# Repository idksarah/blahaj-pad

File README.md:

# 🦈 Blahaj-Pad
Blahaj-Pad is a 3-key macropad for users who need extra space on their keyboard or who simply want to set up their own keyboard values. This repo provides the firmware, CAD files, and gbr files for anyone who wants to recreate this project.

## Tools, Manufactures, Languages Used
- Onshape CAD
- KiCAD
- Python
- KMK
- JLCPCB

## Why'd you make this?
- I really like blahajs.
- Windows' emoji GUI pmo

## Pics

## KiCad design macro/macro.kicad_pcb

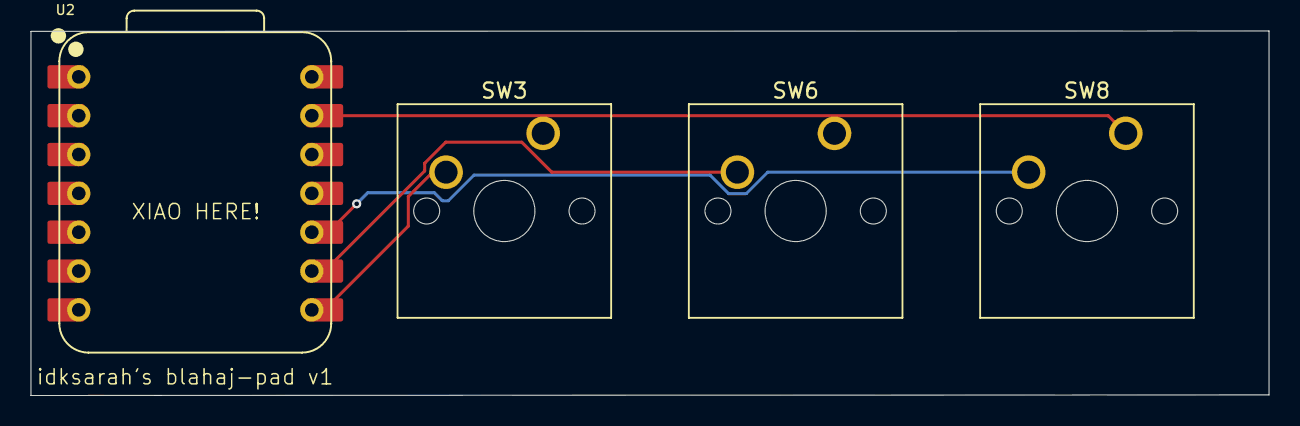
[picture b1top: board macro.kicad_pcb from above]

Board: 2 copper layers, 81.0 x 23.8 mm, 4 parts (0 on the bottom side), 4 nets.

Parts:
SW3, SW6, SW8: SW_Push; SW_Cherry_MX_1.00u_PCB
U2: XIAO-RP2040-DIP

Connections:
GND: SW3.1, SW6.1, SW8.1, U2.13 (GND)
unnamed: SW3.2, U2.8 (GPIO1/RX)
unnamed: SW6.2, U2.9 (GPIO2/SCK)
unnamed: SW8.2, U2.10 (GPIO4/MISO)

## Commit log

2025-04-22 case, pcb, firmware
2025-04-23 remove gap between switches and make case smaller
2025-04-24 usb port front -> back
2025-06-02 firmware
